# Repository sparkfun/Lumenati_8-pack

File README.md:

SparkFun Lumenati 8-pack
========================================

[*SparkFun Lumenati 8-pack (COM-14357)*](https://www.sparkfun.com/products/14357)

The SparkFun Lumenati 8-pack is a coin-sized board equipped with seven APA102C LEDs surrounding the outer edge of the board, with one in the center. Designed to give your projects an edge in their lighting capacity, the 8-pack board can be daisy-chained with other Lumenati boards, thanks to the multiple SMD pads on the back allowing for multiple design options and formations. 

Repository Contents
-------------------

* **/Hardware** - KiCad design files.
* **/Production** - Production panel files.

Documentation
--------------
* **[Example Code](https://github.com/sparkfun/SparkFun_Lumenati_Code)** - Python and Arduino example code for the Lumenati boards.
* **[FastLED Arduino Library](https://github.com/FastLED/FastLED)** - FastLED Arduino library when using the Lumenati with an Arduino.
* **[Hookup Guide](https://learn.sparkfun.com/tutorials/lumenati-hookup-guide)** - Basic hookup guide for the SparkFun Lumenati boards.

License Information
-------------------

This product is _**open source**_! 

Please review the LICENSE.md file for license information. 

If you have any questions or concerns on licensing, please contact techsupport@sparkfun.com.

Distributed as-is; no warranty is given.

- Your friends at SparkFun.

_<COLLABORATION CREDIT>_

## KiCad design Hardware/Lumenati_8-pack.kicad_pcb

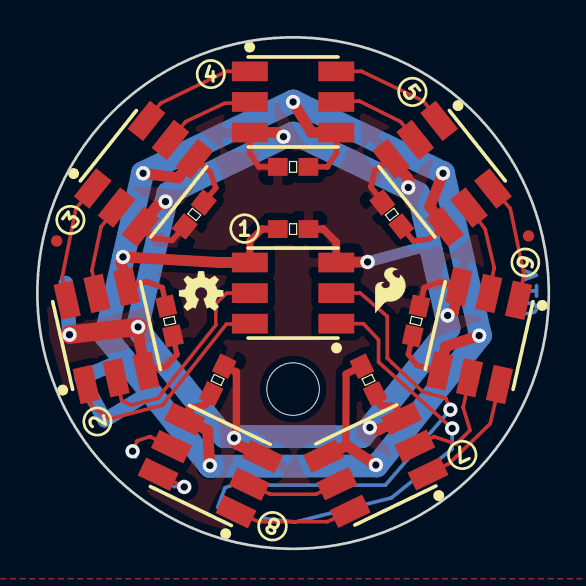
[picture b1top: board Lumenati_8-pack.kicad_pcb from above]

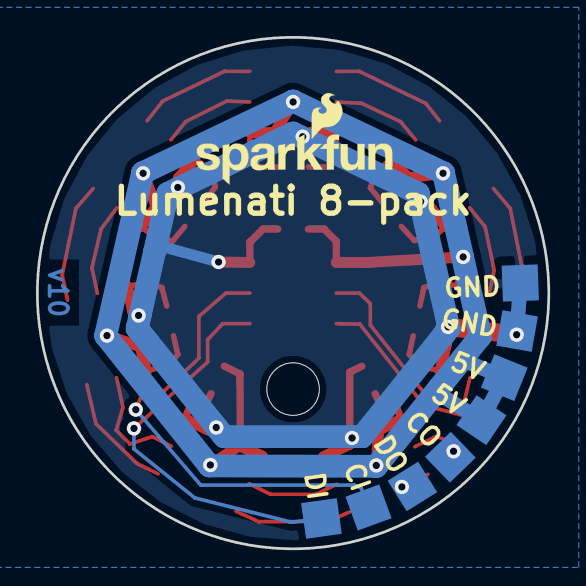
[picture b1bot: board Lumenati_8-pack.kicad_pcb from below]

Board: 2 copper layers, 28.4 x 28.4 mm, 25 parts (8 on the bottom side), 20 nets.

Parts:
C1, C2, C3, C4, C5, C6, C7, C8: C; 0603_revised
J1, J2, J3, J4, J5, J6, J7, J8: M01PTH; solder_pad_2
Ref**: Val**; STAND-OFF_115
U1, U2, U3, U4, U5, U6, U7, U8: APA102; APA102_3

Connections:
+5V: C1.1, C2.1, C3.1, C4.1, C5.1, C6.1, C7.1, C8.1, J3.1, J7.1, U1.4, U2.4, U3.4, U4.4, U5.4, U6.4, U7.4, U8.4
GND: C1.2, C2.2, C3.2, C4.2, C5.2, C6.2, C7.2, C8.2, J4.1, J8.1, U1.3, U2.3, U3.3, U4.3, U5.3, U6.3, U7.3, U8.3
unnamed: J1.1, U1.2
unnamed: J2.1, U1.1
unnamed: J5.1, U8.5
unnamed: J6.1, U8.6
unnamed: U1.5, U2.2
unnamed: U1.6, U2.1
unnamed: U2.5, U3.2
unnamed: U2.6, U3.1
unnamed: U3.5, U4.2
unnamed: U3.6, U4.1
unnamed: U4.5, U5.2
unnamed: U4.6, U5.1
unnamed: U5.5, U6.2
unnamed: U5.6, U6.1
unnamed: U6.5, U7.2
unnamed: U6.6, U7.1
unnamed: U7.5, U8.2
unnamed: U7.6, U8.1

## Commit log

2017-05-17 First commit of HiBeam_8-pack.
2017-05-17 Putting everything into the right directory structure
2017-05-17 Added gerbers, .gitignore and .gitattributes.
2017-05-19 Fixes after double check.
2017-07-05 Silk fixes.
2017-08-11 Changed all the names to Lumenati, updated version to v10.
2017-08-18 Added Fiducials to schematic.
2017-08-18 panel
2017-08-21 Removed paste layer from fiducials.
2017-10-13 Update README.md
    Clean up repository before going live.
2017-10-23 Removing KiCad outout files, updating .gitignore.

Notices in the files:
Hardware/Lumenati_8-pack.kicad_pcb:
Released under the Creative Commons
Attribution Share-Alike 4.0 License
https://creativecommons.org/licenses/by-sa/4.0
